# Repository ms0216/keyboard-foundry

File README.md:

# keyboard foundry

自作キーボードを**現物になる前に機械で確かめながら**作るための作業場。
KLE の配列 1 本から、プレート（STL）・キーマトリクスの基板（KiCad・JLCPCB の規則入り）・
ZMK のシールドを作り、それらが食い違わないことを検査する。

HHKB 分割機（`../2608042258_HHKB_devided`）の開発で積み上げた道具・検査・知識・作法を
抜き出したもの。**核の生成器は、HHKB の発注済みの基板を再現できる**
（キーまわりの全 140 部品の位置・向き・面・フットプリントと、全 244 パッドの結線が一致。
tests/test_regression_hhkb.py）。

## 構成

```
foundry/          共通の核（Python）
  layout.py         KLE → キーの実寸座標。島（分割の左右）に分ける
  matrix.py         キー → (row, col)。基板とファームが同じものを読む
  project.py        機種（projects/<機種>/spec.py + layout.json）を読む
  mech.py           MX・スタビ・ホットスワップの規格値
  plate.py          プレート（build123d）
  pcb.py            未配線の基板（KiCad の Python）。スイッチ・ダイオード・スタビ・穴・JLC 規則
  zmk.py            ZMK シールドの雛形と行列表
  fab_fields.py     発注道具（Fabrication Toolkit）が読む LCSC・面・除外を板に焼く
  drc.py            DRC を指紋つきで記録（警告を隠さない）
  render_pcb.py     基板を絵にする（変わっていなければ描かない・動いた部品を拡大）
  verify.py         寸法・水密・干渉（結果の記憶つき）・図
  inspect_mesh.py / slice_check.py   印刷できるか（近似と、OrcaSlicer で実際にスライス）
  gate.py           発注の門（open-gaps の「せき止めているもの」）
  parts.py          HHKB で確かめた部品と選定理由
  pinmap.py         ピン名 → パッド番号（データシートで裏付け）
  mutate.py         定数を壊して検査が気づくかを測る
  jlcpcb_lookup.py  JLCPCB の API（区分・在庫・単価）
firmware/ zephyr/ ZMK モジュール（乾電池の残量計・打ち止めで停止・状態 LED）
config/ build.yaml ZMK の設定（機種を作ると足される）
lib/              フットプリント（kiswitch の MX ホットスワップ・スタビ、XIAO）
projects/<機種>/  spec.py・layout.json・docs/（台帳）・pcb/
tests/            検査。fixtures/ に HHKB の配列と発注済みの基板から抜き出した事実
tools/kb          機種ごとの操作の入口 / tools/new_project.py
docs/method/      失敗から出た規則
docs/knowledge/   部品・電源・基板・筐体・ZMK・アンテナ・測り方
docs/templates/   台帳の雛形
.claude/          基板が変わったら絵を出して「見ろ」と言う hook
```

## 始め方

```sh
python3.13 -m venv .venv && .venv/bin/pip install -r requirements-dev.txt
.venv/bin/pytest tests -q                              # 全部緑であること

.venv/bin/python3 tools/new_project.py mykb path/to/kle.json
tools/kb mykb plate        # build/mykb/plate_*.stl / .png
tools/kb mykb pcb          # projects/mykb/pcb/unrouted/*.kicad_pcb（KiCad 10 が要る）
```

次にやることは CLAUDE.md の「新しい機種を始める」。

## 要るもの

| 道具 | 何に | 場所の指定 |
|---|---|---|
| Python 3.13 + requirements-dev.txt | 核・検査 | — |
| KiCad 10（同梱の Python と kicad-cli） | 基板の生成・DRC・絵 | `KICAD_PYTHON` `KICAD_CLI` `KICAD_FOOTPRINTS` |
| pdftoppm（poppler） | 基板の絵 | PATH |
| OrcaSlicer | スライスの確認 | `ORCA_SLICER` |
| GitHub Actions | ZMK のビルド（手元に SDK は要らない） | — |

## まだ核に入っていないもの（HHKB を参照実装として読む）

| もの | 理由 | HHKB の場所 |
|---|---|---|
| ケース・組み立て検査（留め方・挿入経路・干渉） | 機種の意匠そのもの。2 台目で共通部分を抜き出す | tools/gen_case.py・gen_assembly.py・envelopes.py |
| MCU 子基板・電源回路・回路図と ERC | 構成が機種ごとに違う（pcb_extra.py で足す） | tools/gen_daughterboard.py・circuit.py・gen_sch.py |
| 配線の仕上げ（GND ビア・手配線の再現） | 配線の品質は手作業から来ていた | tools/finalize_pcb.py・gnd_fanout.py・export_matrix_routing.py |
| .blend での確認 | ケースと一緒に | tools/export_assembly.py・blend_assembly.py |

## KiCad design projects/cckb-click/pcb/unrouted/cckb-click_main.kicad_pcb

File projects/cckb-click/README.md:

# cckb-click

CCKB（HHKB 英語配列・62 キー・19.05 ピッチ・XIAO nRF52840）を、**薄い表面実装のタクトスイッチ**と
**枠の下から入れる軸の無いキーキャップ**で作り直す機種。目標の厚さは約 8.1 mm（CCKB は 14.2）。
方式は Salicylic_acid3 さんの ClickBoard（出どころと条件は [LICENSE](LICENSE)。**非営利に限る**）。

`projects/cckb/`（発注できる状態の CCKB）には手を入れない。だめなら CCKB に戻れる。

## いまの段: 基板・枠・キャップ・ファームまで設計した（独立した監査の前）

**いまの状態は [docs/status.md](docs/status.md)。**残っているものは [docs/open-gaps.md](docs/open-gaps.md) の冒頭。

```
tools/kb cckb-click pcb                                            # 未配線の板
"$KICAD_PYTHON" projects/cckb-click/tools/route_click.py           # 配線（Freerouting 2.3.0 と java が要る）
tools/kb cckb-click fab-fields && tools/kb cckb-click drc          # LCSC の番号・DRC
.venv/bin/python3 projects/cckb-click/click_case.py                # 枠・キャップの STL・断面図・.blend を build/cckb-click/ に
.venv/bin/python3 projects/cckb-click/tools/slice_main.py          # 刷る 4 枚をスライスして G-code を検査
.venv/bin/python3 projects/cckb-click/click_stiffness.py           # たわみの見積もり
.venv/bin/python3 projects/cckb-click/tools/parts_check.py         # 部品の在庫・単価（JLC の API）
.venv/bin/pytest tests/test_cckb_click.py tests/test_cckb_click_pcb.py tests/test_cckb_click_board.py tests/test_cckb_click_case.py -q
tools/kb cckb-click gate                                           # 発注の門（いまは閉）
```

| 読むもの | 何 |
|---|---|
| [docs/status.md](docs/status.md) | **いまの状態**・CCKB との比較・利用者が決めること |
| [docs/open-gaps.md](docs/open-gaps.md) | 発注を止めているもの・実物が来るまで分からないこと |
| [docs/decisions/](docs/decisions/) | 決定の記録（スイッチ・構造・刷り方・試し刷りの結果・基板と枠） |
| [docs/shopping-list.md](docs/shopping-list.md)・[docs/order-steps.md](docs/order-steps.md) | 買う物・基板の頼み方 |
| [docs/printing-guide.md](docs/printing-guide.md)・[docs/assembly-guide.md](docs/assembly-guide.md) | 刷り方・組み立て |
| [docs/coupon-test.md](docs/coupon-test.md) | 試し刷りの手順と結果（2026-10-03 に利用者が刷った） |
| print/ | 精度優先の刷り方のプリセット |
| [docs/provisional-values.md](docs/provisional-values.md) | まだ実測していない値（`[暫定]`） |
| spec.py | 寸法と部品。値ごとに出どころ |

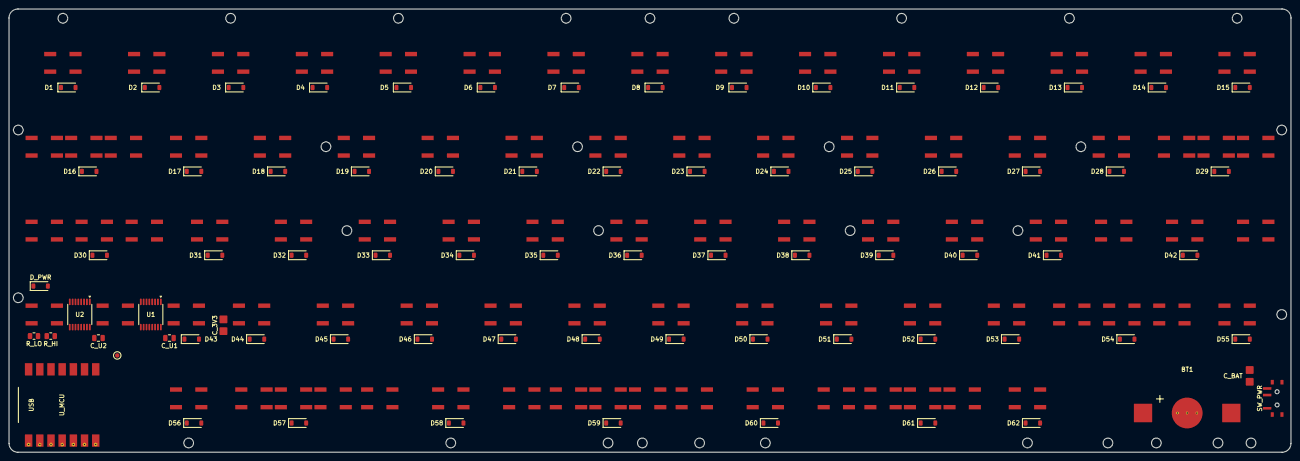
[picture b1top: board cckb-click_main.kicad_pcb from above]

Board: 2 copper layers, 291.2 x 100.7 mm, 191 parts (0 on the bottom side), 91 nets, no tracks yet.

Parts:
BT1: MY-1632-03-R; BAT_MY-1632-03-R
C_3V3: cap_land_unpopulated; C_1206_0805_Land
C_BAT: cap_land_unpopulated; C_1206_0805_Land
C_U1, C_U2: 0.1uF; C_0805_2012Metric
D1, D2, D3, D4, D5, D6, D7, D8, D9, D10, D11, D12, D13, D14, D15, D16, D17, D18, D19, D20, D21, D22, D23, D24, D25, D26, D27, D28, D29, D30, D31, D32, D33, D34, D35, D36, D37, D38, D39, D40, D41, D42, D43, D44, D45, D46, D47, D48, D49, D50, D51, D52, D53, D54, D55, D56, D57, D58, D59, D60, D61, D62: BAT46W; D_SOD-123
D_PWR: BAT46W; D_SOD-123
H0, H1, H2, H3, H4, H5, H6, H7, H8, H9, H10, H11, H12, H13, H14, H15, H16, H17, H18, H19, H20, H21, H22, H23, H24, H25, H26, H27, H28, H29, H30, H31: Hole_M2_2.2
R_HI: 1M; R_0805_2012Metric
R_LO: 1M; R_0805_2012Metric
SW1, SW2, SW3, SW4, SW5, SW6, SW7, SW8, SW9, SW10, SW11, SW12, SW13, SW14, SW15, SW16, SW17, SW18, SW19, SW20, SW21, SW22, SW23, SW24, SW25, SW26, SW27, SW28, SW29, SW30, SW31, SW32, SW33, SW34, SW35, SW36, SW37, SW38, SW39, SW40, SW41, SW42, SW43, SW44, SW45, SW46, SW47, SW48, SW49, SW50, SW51, SW52, SW53, SW54, SW55, SW56, SW57, SW58, SW59, SW60, SW61, SW62: SKRAAWE010; SW_Alps_SKRA_6.2x6.2
SWA16, SWA29, SWA30, SWA42, SWA43, SWA54, SWA57, SWA58, SWA59, SWA60, SWA61: SKRA_side_land_unpopulated; SW_Alps_SKRA_6.2x6.2
SWB16, SWB29, SWB30, SWB42, SWB43, SWB54, SWB57, SWB58, SWB59, SWB60, SWB61: SKRA_side_land_unpopulated; SW_Alps_SKRA_6.2x6.2
SW_PWR: MSK12C02; SW_MSK12C02
TP_VSW: TP_VBAT_SW; TestPoint_Pad_D1.0mm
U1, U2: SN74LVC595APWR; TSSOP-16_4.4x5mm_P0.65mm
U_MCU: XIAO_nRF52840; XIAO_nRF52840_SMD

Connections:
COL0: SW1.1, SW16.1, SW30.1, SWA16.1, SWA30.1, SWB16.1, SWB30.1, U1.15
COL1: SW2.1, SW17.1, SW43.1, SW56.1, SWA43.1, SWB43.1, U1.1
COL2: SW3.1, SW31.1, SW44.1, U1.2
COL3: SW4.1, SW18.1, SW32.1, SW45.1, SW57.1, SWA57.1, SWB57.1, U1.3
COL4: SW5.1, SW19.1, SW33.1, SW46.1, U1.4
COL5: SW6.1, SW20.1, SW34.1, SW47.1, SW58.1, SWA58.1, SWB58.1, U1.5
COL6: SW7.1, SW21.1, SW35.1, SW48.1, SW59.1, SWA59.1, SWB59.1, U1.6
COL7: SW8.1, SW22.1, SW36.1, SW49.1, U1.7
COL8: SW9.1, SW23.1, SW37.1, SW50.1, SW60.1, SWA60.1, SWB60.1, U2.15
COL9: SW10.1, SW24.1, SW38.1, SW51.1, U2.1
COL10: SW11.1, SW25.1, SW39.1, SW52.1, SW61.1, SWA61.1, SWB61.1, U2.2
COL11: SW12.1, SW26.1, SW40.1, SW53.1, U2.3
COL12: SW13.1, SW27.1, SW41.1, SW62.1, U2.4
COL13: SW14.1, SW28.1, SW42.1, SW54.1, SWA42.1, SWA54.1, SWB42.1, SWB54.1, U2.5
COL14: SW15.1, SW29.1, SW55.1, SWA29.1, SWB29.1, U2.6
CS: U1.12, U2.12, U_MCU.D7
GND: BT1.2, C_3V3.2, C_BAT.2, C_U1.2, C_U2.2, R_LO.2, SW_PWR.4, U1.8, U1.13, U2.8, U2.13, U_MCU.GND
ROW0: D1.1, D2.1, D3.1, D4.1, D5.1, D6.1, D7.1, D8.1, D9.1, D10.1, D11.1, D12.1, D13.1, D14.1, D15.1, U_MCU.D2
ROW1: D16.1, D17.1, D18.1, D19.1, D20.1, D21.1, D22.1, D23.1, D24.1, D25.1, D26.1, D27.1, D28.1, D29.1, U_MCU.D3
ROW2: D30.1, D31.1, D32.1, D33.1, D34.1, D35.1, D36.1, D37.1, D38.1, D39.1, D40.1, D41.1, D42.1, U_MCU.D4
ROW3: D43.1, D44.1, D45.1, D46.1, D47.1, D48.1, D49.1, D50.1, D51.1, D52.1, D53.1, D54.1, D55.1, U_MCU.D5
ROW4: D56.1, D57.1, D58.1, D59.1, D60.1, D61.1, D62.1, U_MCU.D6
SPI_MOSI: U1.14, U_MCU.D10
SPI_SCK: U1.11, U2.11, U_MCU.D8
SW1_D: D1.2, SW1.2
SW2_D: D2.2, SW2.2
SW3_D: D3.2, SW3.2
SW4_D: D4.2, SW4.2
SW5_D: D5.2, SW5.2
SW6_D: D6.2, SW6.2
SW7_D: D7.2, SW7.2
SW8_D: D8.2, SW8.2
SW9_D: D9.2, SW9.2
SW10_D: D10.2, SW10.2
SW11_D: D11.2, SW11.2
SW12_D: D12.2, SW12.2
SW13_D: D13.2, SW13.2
SW14_D: D14.2, SW14.2
SW15_D: D15.2, SW15.2
SW16_D: D16.2, SW16.2, SWA16.2, SWB16.2
SW17_D: D17.2, SW17.2
SW18_D: D18.2, SW18.2
SW19_D: D19.2, SW19.2
SW20_D: D20.2, SW20.2
SW21_D: D21.2, SW21.2
SW22_D: D22.2, SW22.2
SW23_D: D23.2, SW23.2
SW24_D: D24.2, SW24.2
SW25_D: D25.2, SW25.2
SW26_D: D26.2, SW26.2
SW27_D: D27.2, SW27.2
SW28_D: D28.2, SW28.2
SW29_D: D29.2, SW29.2, SWA29.2, SWB29.2
SW30_D: D30.2, SW30.2, SWA30.2, SWB30.2
SW31_D: D31.2, SW31.2
SW32_D: D32.2, SW32.2
SW33_D: D33.2, SW33.2
SW34_D: D34.2, SW34.2
SW35_D: D35.2, SW35.2
SW36_D: D36.2, SW36.2
SW37_D: D37.2, SW37.2
SW38_D: D38.2, SW38.2
SW39_D: D39.2, SW39.2
SW40_D: D40.2, SW40.2
SW41_D: D41.2, SW41.2
SW42_D: D42.2, SW42.2, SWA42.2, SWB42.2
SW43_D: D43.2, SW43.2, SWA43.2, SWB43.2
SW44_D: D44.2, SW44.2
SW45_D: D45.2, SW45.2
SW46_D: D46.2, SW46.2
SW47_D: D47.2, SW47.2
SW48_D: D48.2, SW48.2
SW49_D: D49.2, SW49.2
SW50_D: D50.2, SW50.2
SW51_D: D51.2, SW51.2
SW52_D: D52.2, SW52.2
SW53_D: D53.2, SW53.2
SW54_D: D54.2, SW54.2, SWA54.2, SWB54.2
SW55_D: D55.2, SW55.2
SW56_D: D56.2, SW56.2
SW57_D: D57.2, SW57.2, SWA57.2, SWB57.2
SW58_D: D58.2, SW58.2, SWA58.2, SWB58.2
SW59_D: D59.2, SW59.2, SWA59.2, SWB59.2
SW60_D: D60.2, SW60.2, SWA60.2, SWB60.2
SW61_D: D61.2, SW61.2, SWA61.2, SWB61.2
SW62_D: D62.2, SW62.2
U1_U2: U1.9, U2.14
V3V3: C_3V3.1, C_U1.1, C_U2.1, D_PWR.1, U1.10, U1.16, U2.10, U2.16, U_MCU.3V3
VBAT_IN: BT1.1, SW_PWR.2
VBAT_SENSE: R_HI.2, R_LO.1, U_MCU.D0
VBAT_SW: C_BAT.1, D_PWR.2, R_HI.1, SW_PWR.3, TP_VSW.1
